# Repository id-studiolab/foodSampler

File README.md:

# foodSampler
Food sampler is a project to collect user data about their food consumption.
It consist of a series of devices equipped with buttons who can send and save data to a server using Lora protocol.

## The device
The devices are based on adafruit feather lora baord, and make use of a custom pcb.
They run on buttery and try to send messages to the lora network every 10 minutes.
once a button is pressed, they connect to the server and send out the data. A button cannot be pressed continuosly... a trasmission need to finish before a new message can be sent.
Arduino code, pcb design and more information on how to configure the library can be found inside the device folder.

## The server
The device communicate via a gateway to the things network, each device need to be configured and provisioned via ttn platform before it can send data to the server.
The server listens for incoming messages from the things network and saves the data to a mongodb DB. The data are accessible trough rest api.
More information on how to deploy the server and which api are accessible can be found in the server folder.

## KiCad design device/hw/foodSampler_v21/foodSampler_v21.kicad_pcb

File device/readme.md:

To set up the feather install the MCCI LoRaWAN LMIC library via the library manager.

Then navigate to the library folder and modify the file project_config/lmic_project_config.h with the correct frequency

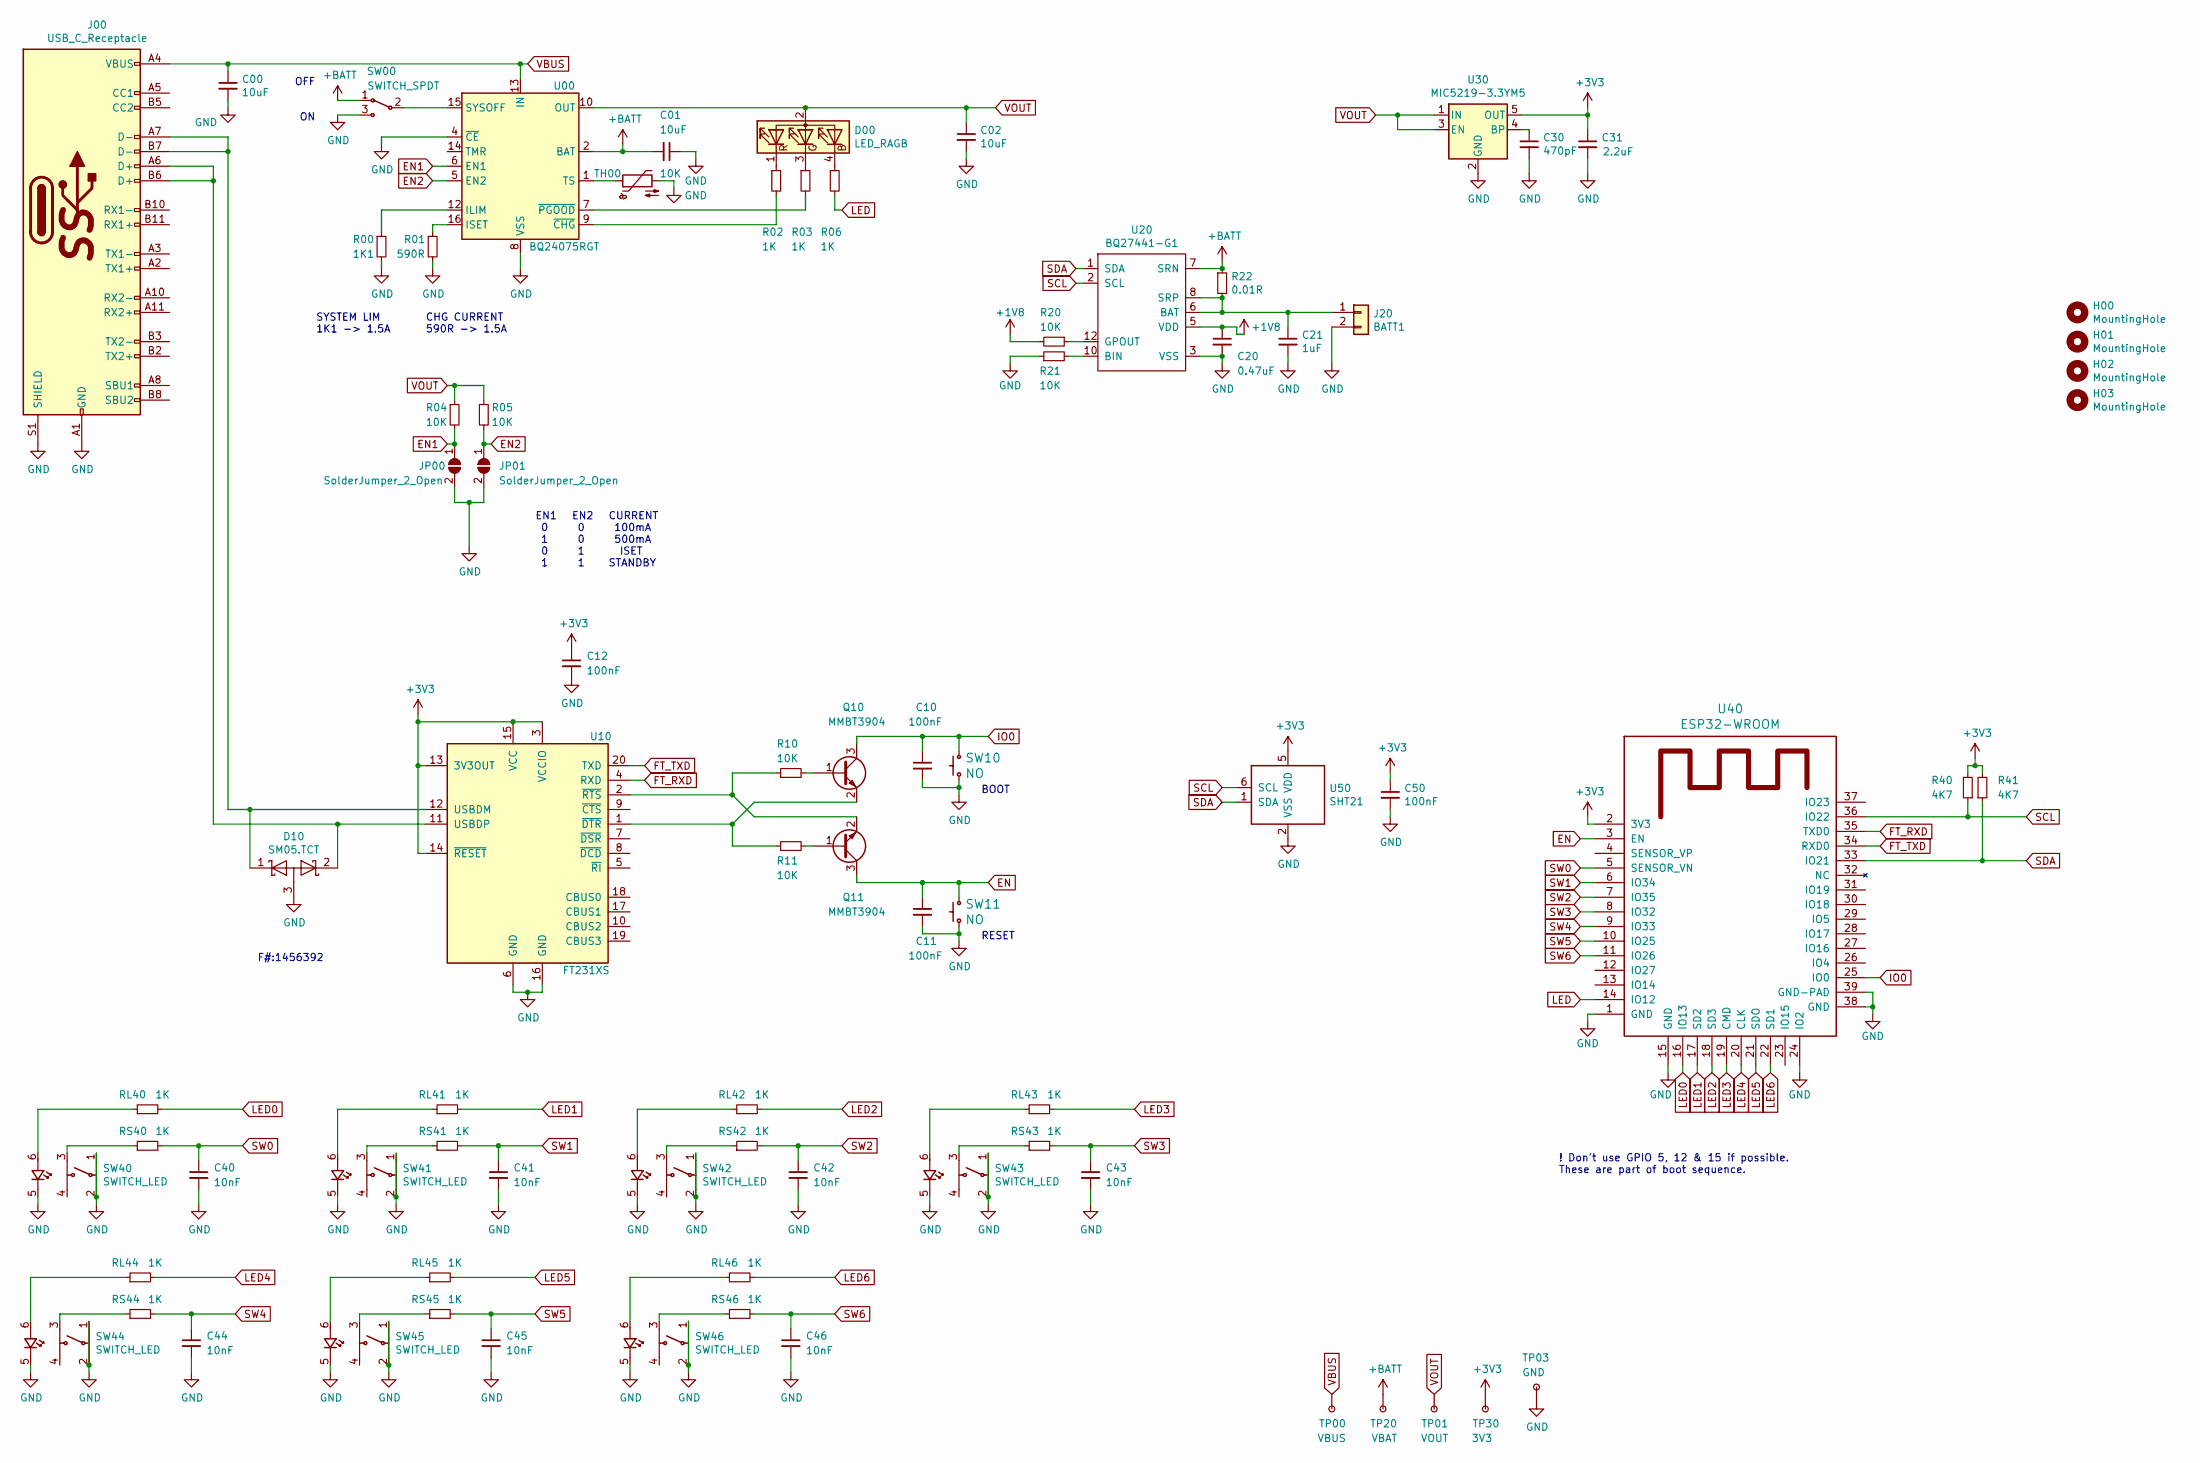
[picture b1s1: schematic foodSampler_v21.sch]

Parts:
C00, C01, C02: 10uF; C_0805_2012Metric
C10, C11, C12, C50: 100nF; C_0603_1608Metric
C20: 0.47uF; C_0603_1608Metric
C21: 1uF; C_0603_1608Metric
C30: 470pF; C_0603_1608Metric
C31: 2.2uF; CP_EIA-3216-10_Kemet-I
C40, C41, C42, C43, C44, C45, C46: 10nF; C_0603_1608Metric
D00: LED_RAGB; SMD_RGB_SIDE-APFA3010LSEEZGKQBKC
D10: SM05.TCT; SOT-23
H00, H01, H02, H03: MountingHole; MountingHole_3.2mm_M3
J00: USB_C_Receptacle; CUI_USB-C_UJ31-CH-3-MSMT-TR-67
J20: BATT1; JST_B2B-PH-K-S_SUNK
JP00, JP01: SolderJumper_2_Open; SolderJumper-2_P1.3mm_Open_RoundedPad1.0x1.5mm
Q10, Q11: MMBT3904; SOT-23
R00: 1K1; R_0603_1608Metric
R01: 590R; R_0603_1608Metric
R02, R03, R06: 1K; R_0603_1608Metric
R04, R05, R10, R11, R20, R21: 10K; R_0603_1608Metric
R22: 0.01R; C_1206_3216Metric
R40, R41: 4K7; R_0603_1608Metric
RL40, RL41, RL42, RL43, RL44, RL45, RL46: 1K; R_0603_1608Metric
RS40, RS41, RS42, RS43, RS44, RS45, RS46: 1K; R_0603_1608Metric
SW00: SWITCH_SPDT; C&K-OS102011MS2QN1_side_mount
SW10, SW11: NO; SW_SPST_4x3
SW40, SW41, SW42, SW43, SW44, SW45, SW46: SWITCH_LED; MICRO_SW_LED
TH00: 10K; R_Axial_DIN0204_L3.6mm_D1.6mm_P2.54mm_Vertical
TP00: VBUS; TEST_PAD_HOLE_1mm
TP01: VOUT; TEST_PAD_HOLE_1mm
TP03: GND; TEST_PAD_HOLE_1mm
TP20: VBAT; TEST_PAD_HOLE_1mm
TP30: 3V3; TEST_PAD_HOLE_1mm
U00: BQ24075RGT; VQFN-16-1EP_3x3mm_P0.5mm_EP1.6x1.6mm
U10: FT231XS; SSOP-20_3.9x8.7mm_P0.635mm
U20: BQ27441-G1; Texas_S-PDSO-N12
U30: MIC5219-3.3YM5; SOT-23-5
U40: ESP32-WROOM; ESP32-WROOM-32
U50: SHT21

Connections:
+1V8: C20.1, R20.2, U20.5 (VDD)
+3V3: C12.1, C31.1, C50.1, R40.2, R41.2, TP30.1, U10.3 (VCCIO), U10.13 (3V3OUT), U10.14 (~RESET), U10.15 (VCC), U30.5 (OUT), U40.2 (3V3), U50.5 (VDD)
+BATT: C01.2, R22.1, SW00.1, TP20.1, U00.2 (BAT), U00.3 (BAT), U20.7 (SRN)
EN: C11.1, Q11.3 (C), SW11.2 (B0), U40.3 (EN)
EN1: JP00.1 (A), R04.2, U00.6 (EN1)
EN2: JP01.1 (A), R05.2, U00.5 (EN2)
FT_RXD: U10.4 (RXD), U40.35 (TXD0)
FT_TXD: U10.20 (TXD), U40.34 (RXD0)
GND: C00.2, C01.1, C02.2, C10.2, C11.2, C12.2, C20.2, C21.2, C30.2, C31.2, C40.2, C41.2, C42.2, C43.2, C44.2, C45.2, C46.2, C50.2, D10.3 (A), J00.A1 (GND), J00.A12 (GND), J00.B1 (GND), J00.B12 (GND), J00.S1 (SHIELD), J20.2, JP00.2 (B), JP01.2 (B), R00.2, R01.2, R21.1, SW00.3, SW10.1 (A0), SW11.1 (A0), SW40.1, SW40.2, SW40.5, SW41.1, SW41.2, SW41.5, SW42.1, SW42.2, SW42.5, SW43.1, SW43.2, SW43.5, SW44.1, SW44.2, SW44.5, SW45.1, SW45.2, SW45.5, SW46.1, SW46.2, SW46.5, TH00.2, TP03.1, U00.4 (~CE), U00.8 (VSS), U00.17 (VSS), U10.6 (GND), U10.16 (GND), U20.3 (VSS), U30.2 (GND), U40.1 (GND), U40.15 (GND), U40.24 (IO2), U40.38 (GND), U40.39 (GND-PAD), U50.2 (VSS)
IO0: C10.1, Q10.3 (C), SW10.2 (B0), U40.25 (IO0)
LED: R06.2, U40.14 (IO12)
LED0: RL40.2, U40.16 (IO13)
LED1: RL41.2, U40.17 (SD2)
LED2: RL42.2, U40.18 (SD3)
LED3: RL43.2, U40.19 (CMD)
LED4: RL44.2, U40.20 (CLK)
LED5: RL45.2, U40.21 (SDO)
LED6: RL46.2, U40.22 (SD1)
unnamed: C21.1, J20.1, R22.2, U20.6 (BAT), U20.8 (SRP)
unnamed: C30.1, U30.4 (BP)
unnamed: D00.1 (RK), R02.1
unnamed: D00.3 (GK), R03.1
unnamed: D00.4 (BK), R06.1
unnamed: D10.1 (K), J00.A7 (D-), J00.B7 (D-), U10.12 (USBDM)
unnamed: D10.2 (K), J00.A6 (D+), J00.B6 (D+), U10.11 (USBDP)
unnamed: Q10.1 (B), R10.2
unnamed: Q10.2 (E), R11.1, U10.1 (~DTR)
unnamed: Q11.1 (B), R11.2
unnamed: Q11.2 (E), R10.1, U10.2 (~RTS)
unnamed: R00.1, U00.12 (ILIM)
unnamed: R01.1, U00.16 (ISET)
unnamed: R02.2, U00.9 (~CHG)
unnamed: R03.2, U00.7 (~PGOOD)
unnamed: R20.1, U20.12 (GPOUT)
unnamed: R21.2, U20.10 (BIN)
unnamed: RL40.1, SW40.6
unnamed: RL41.1, SW41.6
unnamed: RL42.1, SW42.6
unnamed: RL43.1, SW43.6
unnamed: RL44.1, SW44.6
unnamed: RL45.1, SW45.6
unnamed: RL46.1, SW46.6
unnamed: RS40.1, SW40.3
unnamed: RS41.1, SW41.3
unnamed: RS42.1, SW42.3
unnamed: RS43.1, SW43.3
unnamed: RS44.1, SW44.3
unnamed: RS45.1, SW45.3
unnamed: RS46.1, SW46.3
unnamed: SW00.2, U00.15 (SYSOFF)
unnamed: TH00.1, U00.1 (TS)
SCL: R40.1, U20.2 (SCL), U40.36 (IO22), U50.6 (SCL)
SDA: R41.1, U20.1 (SDA), U40.33 (IO21), U50.1 (SDA)
SW0: C40.1, RS40.2, U40.5 (SENSOR_VN)
SW1: C41.1, RS41.2, U40.6 (IO34)
SW2: C42.1, RS42.2, U40.7 (IO35)
SW3: C43.1, RS43.2, U40.8 (IO32)
SW4: C44.1, RS44.2, U40.9 (IO33)
SW5: C45.1, RS45.2, U40.10 (IO25)
SW6: C46.1, RS46.2, U40.11 (IO26)
VBUS: C00.1, J00.A4 (VBUS), J00.A9 (VBUS), J00.B4 (VBUS), J00.B9 (VBUS), TP00.1, U00.13 (IN)
VOUT: C02.1, D00.2 (A), R04.1, R05.1, TP01.1, U00.10 (OUT), U00.11 (OUT), U30.1 (IN), U30.3 (EN)

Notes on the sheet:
F#:1456392
RESET
BOOT
! Don’t use GPIO 5, 12 & 15 if possible. These are part of boot sequence.
CHG CURRENT 590R -> 1.5A
SYSTEM LIM 1K1 -> 1.5A
EN1 0 1 0 1
EN2 0 0 1 1
CURRENT 100mA 500mA ISET STANDBY
OFF ON

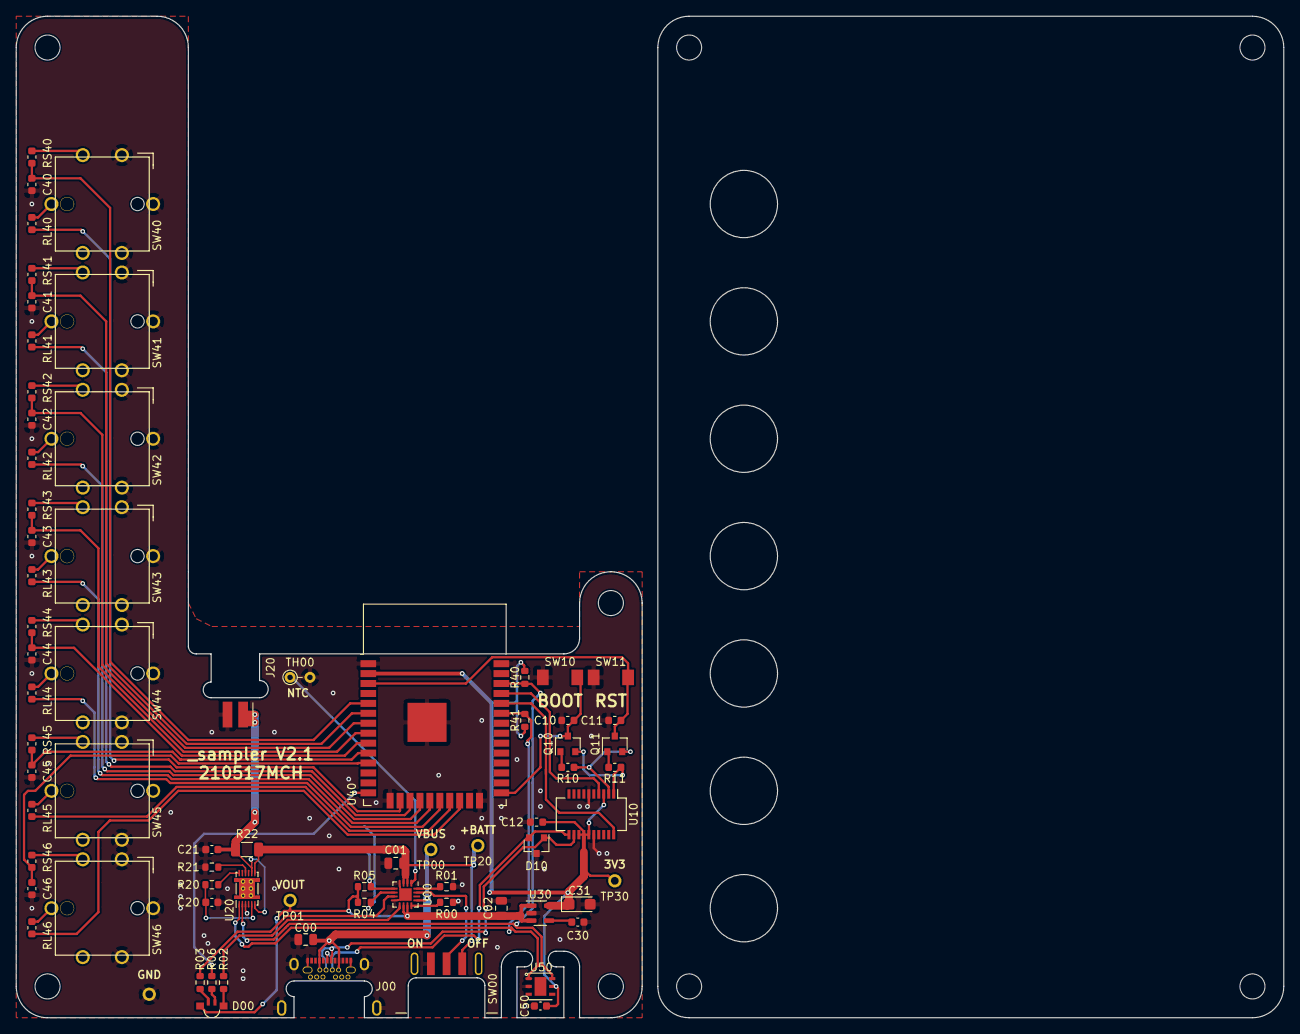
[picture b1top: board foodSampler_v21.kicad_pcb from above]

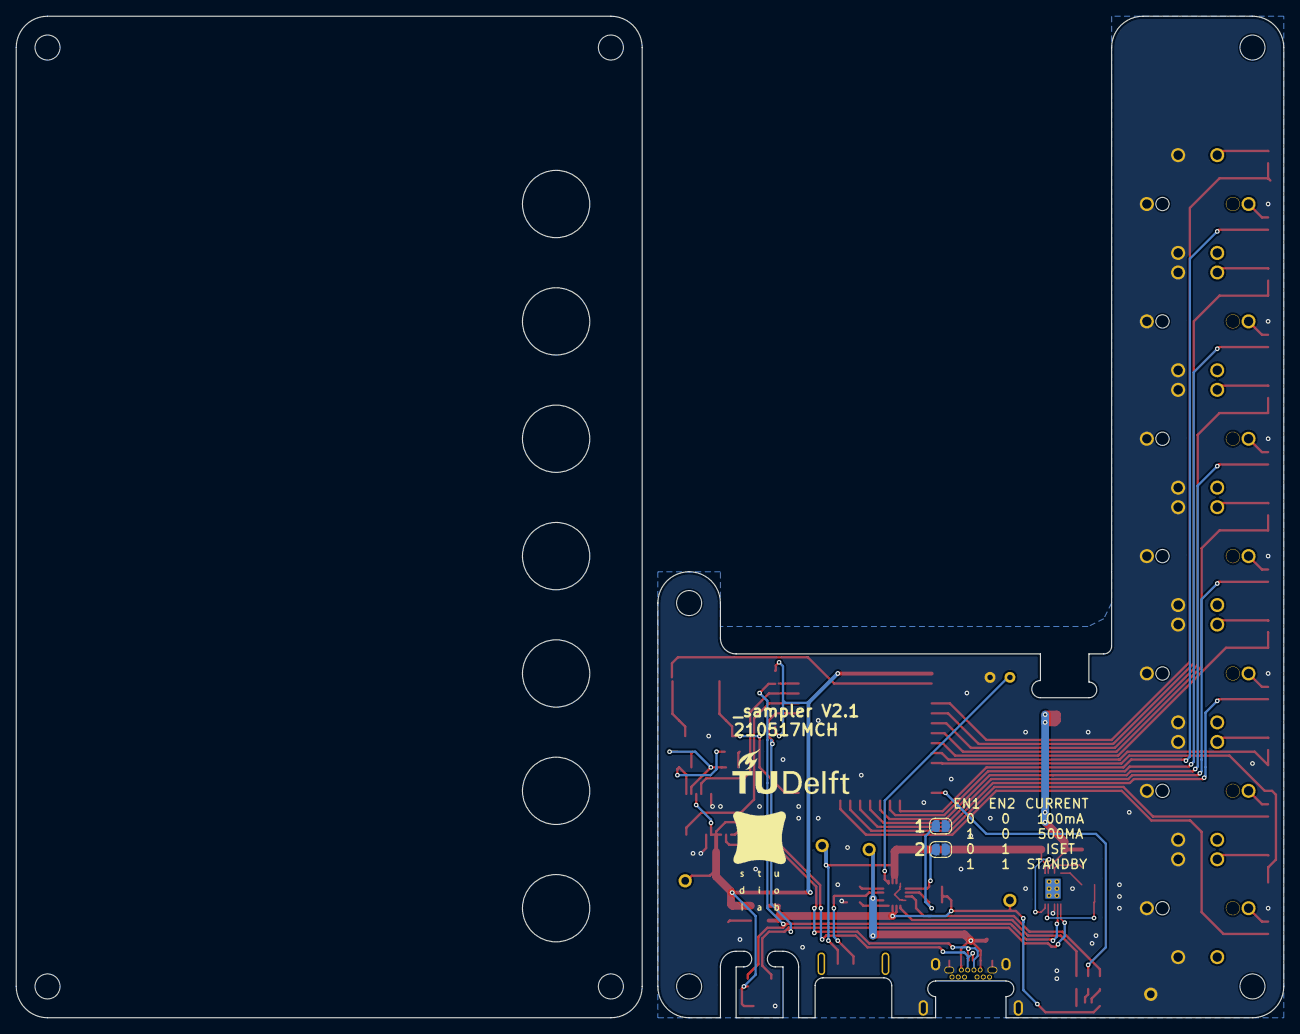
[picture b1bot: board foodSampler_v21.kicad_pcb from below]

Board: 2 copper layers, 162.0 x 128.0 mm, 84 parts (2 on the bottom side), 62 nets.

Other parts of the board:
H01#2, H01#3, H01#4, H01#5: MountingHole; MountingHole_3.2mm_M3

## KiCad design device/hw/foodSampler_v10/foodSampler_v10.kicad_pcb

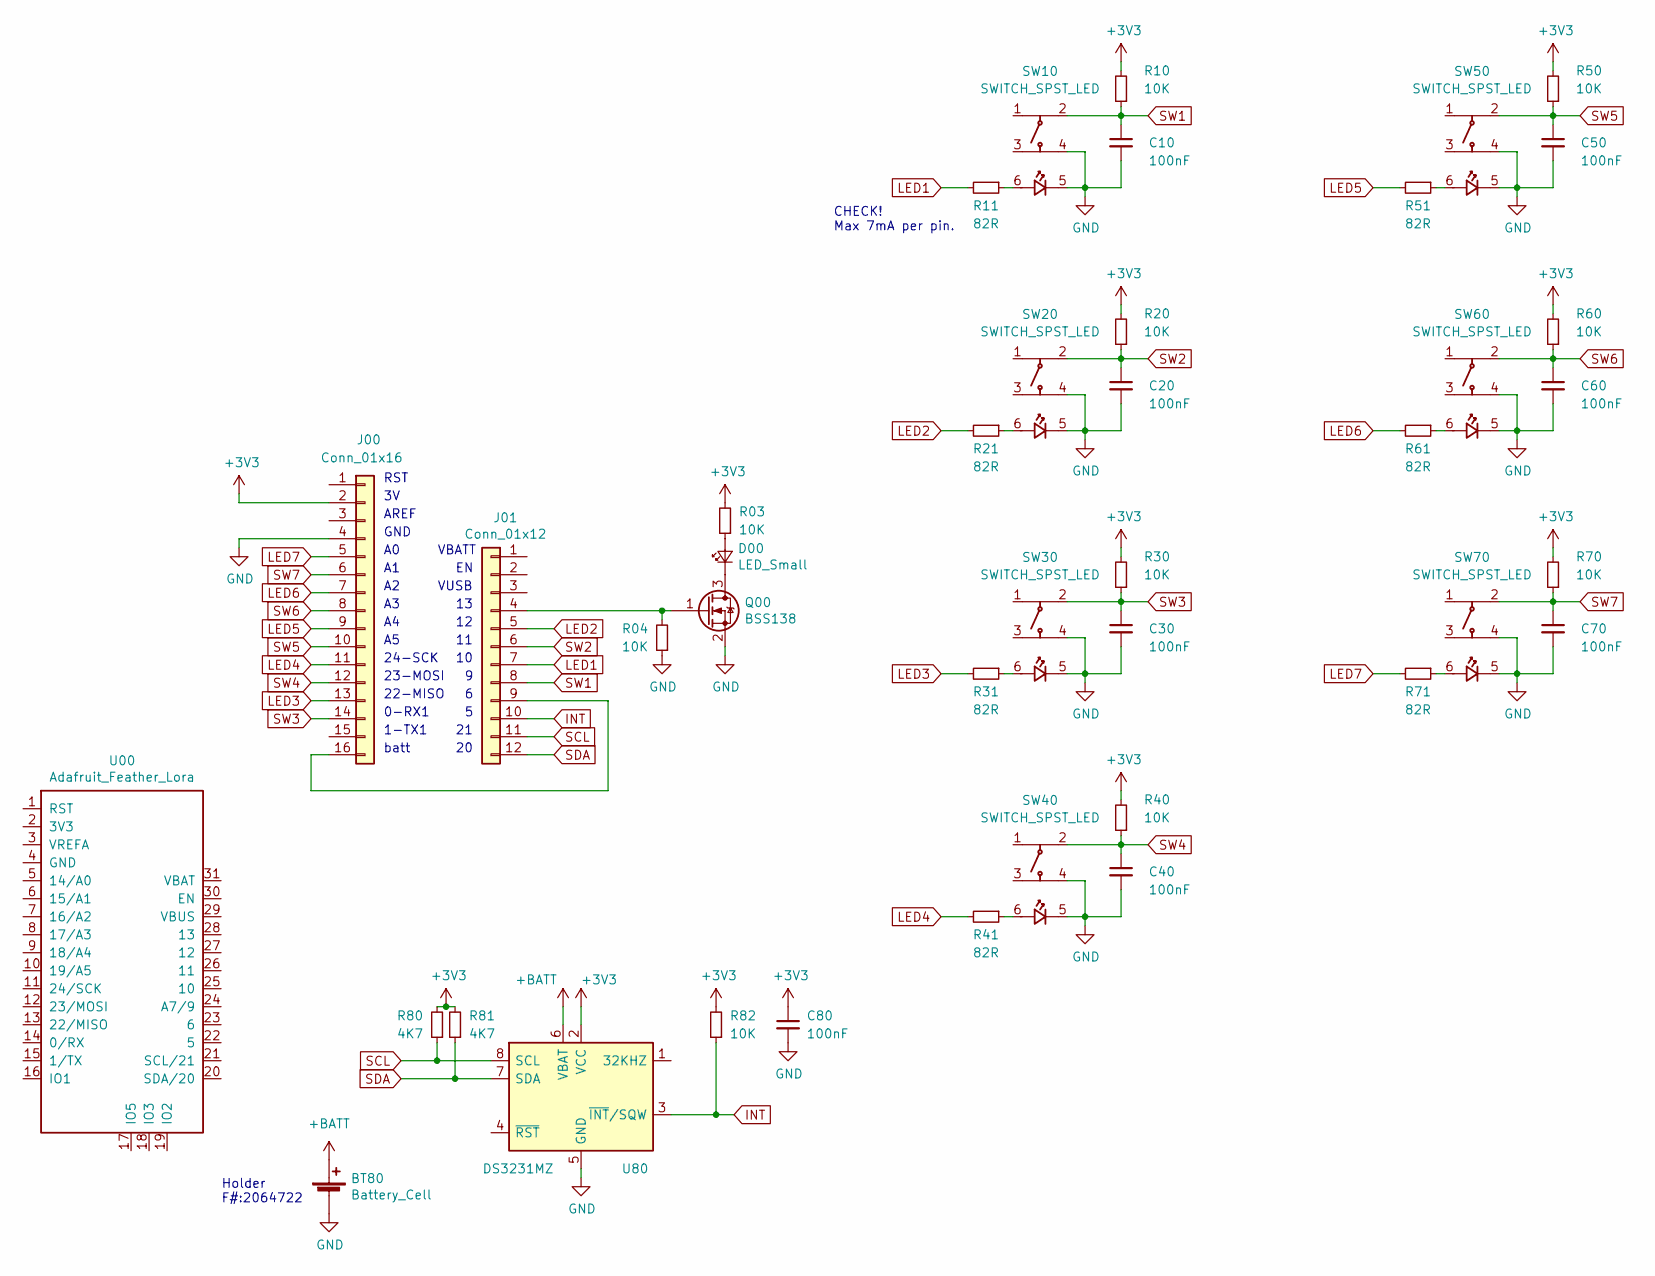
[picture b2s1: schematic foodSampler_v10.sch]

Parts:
BT80: Battery_Cell; CH291-1220LF
C10, C20, C30, C40, C50, C60, C70, C80: 100nF; C_0603_1608Metric
D00: LED_Small; LED_1206_3216Metric
J00: Conn_01x16; PinHeader_1x16_P2.54mm_Vertical_SMD_Pin1Left
J01: Conn_01x12; PinHeader_1x12_P2.54mm_Vertical_SMD_Pin1Left
Q00: BSS138; SOT-23
R03, R04, R10, R20, R30, R40, R50, R60, R70, R82: 10K; R_0603_1608Metric
R11, R21, R31, R41, R51, R61, R71: 82R; R_0603_1608Metric
R80, R81: 4K7; R_0603_1608Metric
SW10, SW20, SW30, SW40, SW50, SW60, SW70: SWITCH_SPST_LED; MICRO_SW_LED
U00: Adafruit_Feather_Lora; Adafruit Feather LORA
U80: DS3231MZ; SOIC-8_3.9x4.9mm_P1.27mm

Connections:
+3V3: C80.1, J00.2, R03.2, R10.2, R20.2, R30.2, R40.2, R50.2, R60.2, R70.2, R80.2, R81.2, R82.2, U80.2 (VCC)
+BATT: BT80.1 (+), U80.6 (VBAT)
GND: BT80.2 (-), C10.2, C20.2, C30.2, C40.2, C50.2, C60.2, C70.2, C80.2, J00.4, Q00.2 (S), R04.1, SW10.4, SW10.5, SW20.4, SW20.5, SW30.4, SW30.5, SW40.4, SW40.5, SW50.4, SW50.5, SW60.4, SW60.5, SW70.4, SW70.5, U80.5 (GND)
INT: J01.10, R82.1, U80.3 (~INT~/SQW)
LED1: J01.7, R11.2
LED2: J01.5, R21.2
LED3: J00.13, R31.2
LED4: J00.11, R41.2
LED5: J00.9, R51.2
LED6: J00.7, R61.2
LED7: J00.5, R71.2
unnamed: D00.1 (K), Q00.3 (D)
unnamed: D00.2 (A), R03.1
unnamed: J00.16, J01.9
unnamed: J01.4, Q00.1 (G), R04.2
unnamed: R11.1, SW10.6
unnamed: R21.1, SW20.6
unnamed: R31.1, SW30.6
unnamed: R41.1, SW40.6
unnamed: R51.1, SW50.6
unnamed: R61.1, SW60.6
unnamed: R71.1, SW70.6
SCL: J01.11, R80.1, U80.8 (SCL)
SDA: J01.12, R81.1, U80.7 (SDA)
SW1: C10.1, J01.8, R10.1, SW10.2
SW2: C20.1, J01.6, R20.1, SW20.2
SW3: C30.1, J00.14, R30.1, SW30.2
SW4: C40.1, J00.12, R40.1, SW40.2
SW5: C50.1, J00.10, R50.1, SW50.2
SW6: C60.1, J00.8, R60.1, SW60.2
SW7: C70.1, J00.6, R70.1, SW70.2

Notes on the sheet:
CHECK! Max 7mA per pin.
Holder F#:2064722
batt
1-TX1
0-RX1
22-MISO
23-MOSI
24-SCK
GND
AREF
RST
VUSB
VBATT

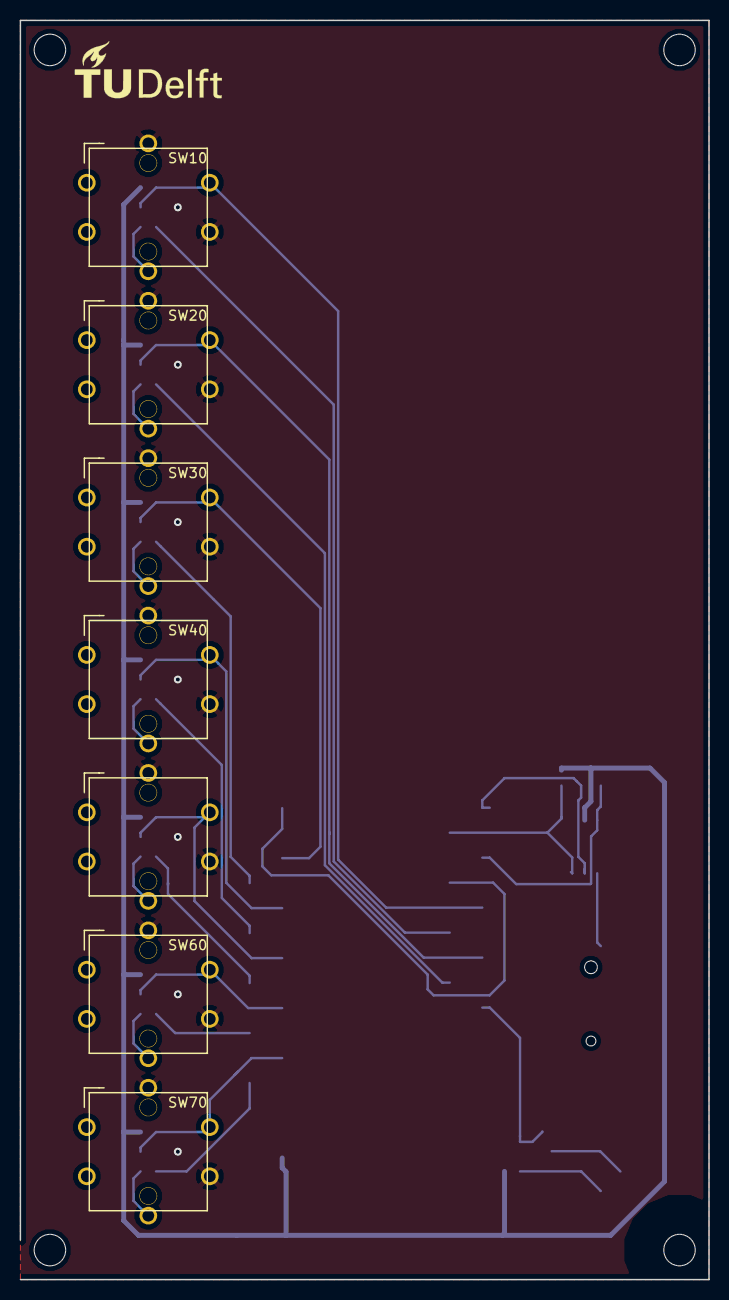
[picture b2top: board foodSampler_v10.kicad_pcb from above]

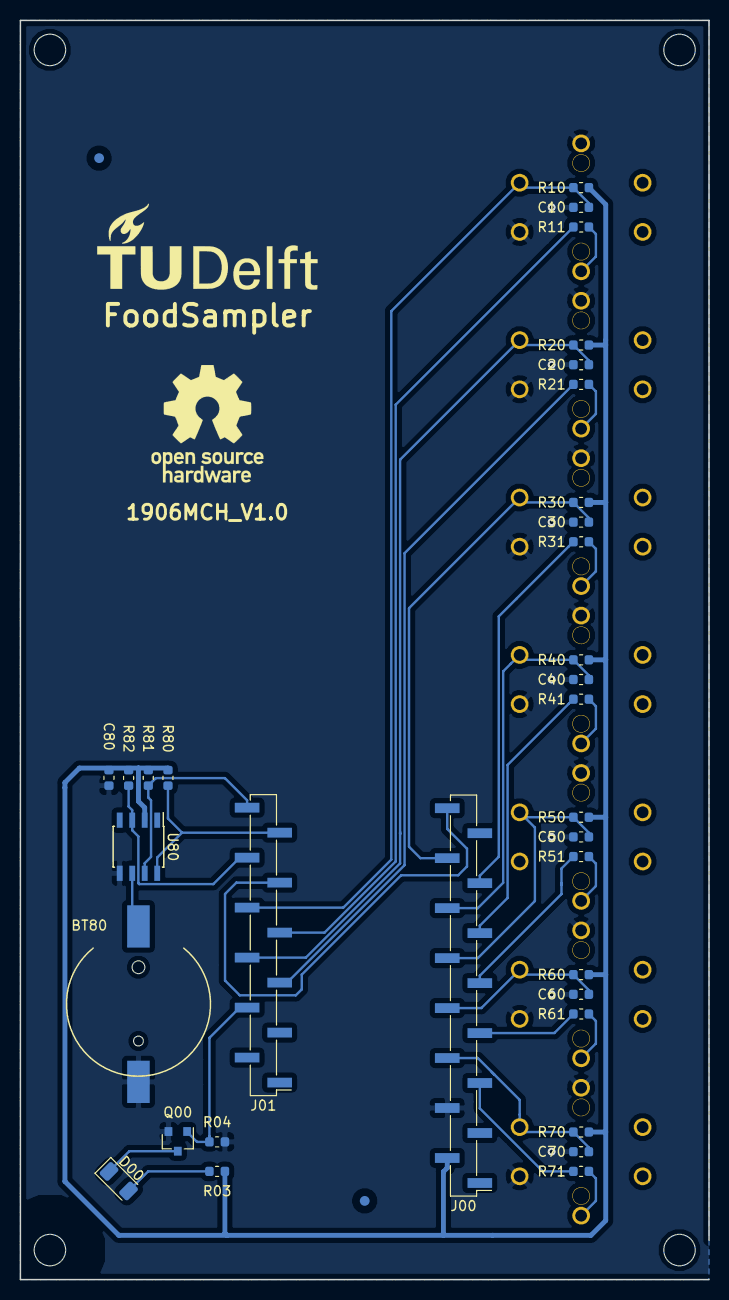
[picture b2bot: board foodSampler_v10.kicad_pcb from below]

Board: 2 copper layers, 70.0 x 128.0 mm, 40 parts (33 on the bottom side), 31 nets.

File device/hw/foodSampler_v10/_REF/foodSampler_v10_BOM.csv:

"Id";"Designator";"Package";"Quantity";"Designation";"Supplier and ref";
1;"J00";"PinHeader_1x16_P2.54mm_Vertical_SMD_Pin1Left";1;"Conn_01x16";;;
2;"C10,C20,C30,C40,C50,C60,C70,C80";"C_0603_1608Metric";8;"100nF";;;
3;"R10,R20,R30,R40,R50,R60,R70,R03,R82,R04";"R_0603_1608Metric";10;"10K";;;
4;"R11,R21,R31,R41,R51,R61,R71";"R_0603_1608Metric";7;"82R";;;
5;"SW10,SW20,SW30,SW40,SW50,SW60,SW70";"MICRO_SW_LED";7;"SWITCH_SPST_LED";;;
6;"REF**";"LIPO_3V7_2A_50x60";1;"LIPO_3V7_2A_50x60";;;
7;"J01";"PinHeader_1x12_P2.54mm_Vertical_SMD_Pin1Left";1;"Conn_01x12";;;
8;"R80,R81";"R_0603_1608Metric";2;"4K7";;;
9;"U80";"SOIC-8_3.9x4.9mm_P1.27mm";1;"DS3231MZ";;;
10;"D00";"LED_1206_3216Metric";1;"LED_Small";;;
11;"BT80";"CH291-1220LF";1;"Battery_Cell";;;
12;"Q00";"SOT-23";1;"BSS138";;;
13;"REF**,REF**,REF**,REF**";"MountingHole_3.2mm_M3_DIN965";4;"MountingHole_3.2mm_M3_DIN965";;;
14;"REF**,REF**";"Fiducial_1mm_Dia_2.54mm_Outer_CopperBottom";2;"Fiducial_1mm_Dia_2.54mm_Outer_CopperBottom";;;
15;"G***";"TUDelft_15x5.9";1;"LOGO";;;
16;"REF**";"OSHW-Logo_11.4x12mm_SilkScreen";1;"OSHW-Logo_11.4x12mm_SilkScreen";;;
17;"G***";"TUDelft_22.5x8.8";1;"LOGO";;;

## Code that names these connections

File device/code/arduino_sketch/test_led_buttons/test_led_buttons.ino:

#define BUT0   9
#define BUT1   11
#define BUT2   0
#define BUT3   1
#define BUT4   A5
#define BUT5   A3
#define BUT6   A1
#define BATPIN A7
#define LED    13

#define LED0   10
#define LED1   12
#define LED2   22
#define LED3   24
#define LED4   A4
#define LED5   A2
#define LED6   A0

int buttons[] = {BUT0, BUT1, BUT2, BUT3, BUT4, BUT5, BUT6, BUT6};
int leds[] = {LED0, LED1, LED2, LED3, LED4, LED5, LED6, LED6};

void setup() {

  for (int i = 0; i < 7; i++) {
    pinMode(buttons[i], INPUT_PULLUP);
    pinMode(leds[i], OUTPUT);
  }
  Serial.begin(9600);
}

void loop() {
  for (int i = 0; i < 7; i++) {
    if (digitalRead(buttons[i])==LOW){
      digitalWrite(leds[i],HIGH);
      Serial.print("button "); 
      Serial.print(i);
      Serial.println(" was pressed");
    }else{
      digitalWrite(leds[i],LOW);
    }
  }
}

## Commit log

2019-03-29 added readme
2019-04-11 add server boilerplate
2019-04-17 intial rest api development
2019-04-18 events model
2019-04-18 created basic api
2019-04-26 got harware working
2019-04-26 add instruction on how to modify the library
2019-04-26 done parsing data from device - need to modify device property in rest api
2019-05-08 updated server api
2019-05-15 added mosca broker and code to forward messages to mqtt
2019-05-15 ready for first test
2019-05-15 modified mosquitto publishing address
2019-05-15 fixes variable missing
2019-05-15 fix wrong addressess for different environment
2019-05-15 Added working protoype code
2019-05-30 fixes apidoc
2019-05-30 ported project to gulp 4
2019-05-30 removed wrong dependency
2019-06-19 add authentication
2019-06-19 schematic added
2019-06-21 tryign to fix things
2019-06-21 V1.0, all working
2019-06-21 fixes authentication
2019-06-21 modified app name
2019-06-21 missind gependency
2019-06-21 typo
2019-06-21 all working
2019-06-21 add files to keep credentials
2019-06-21 led solved
2019-06-21 led solved + flash sequences
2019-06-21 fixes server crashing when data is coming from unknown device
2019-06-21 debug mode and rtc added
2019-07-01 regenerated doc
2019-07-01 re-enabled account creation
2019-07-02 impreoved doc and fixed minor bug
2019-07-02 add filter mechanism for api
2019-08-20 adding cors support to server
2019-08-20 fixes filter events by date range
2019-08-21 fixes dates interval not working
2019-10-03 created new case
2019-10-28 updated 3d printed files
2019-10-28 provisioned all the devices id
2019-10-28 add nickname to device
2019-10-28 remove authentification to create events
2019-10-29 Bump mongoose from 5.5.11 to 5.7.5 in /server/foodsampler
    Bumps [mongoose](https://github.com/Automattic/mongoose) from 5.5.11 to 5.7.5.
    - [Release notes](https://github.com/Automattic/mongoose/releases)
    - [Changelog](https://github.com/Automattic/mongoose/blob/master/History.md)
    - [Commits](https://github.com/Automattic/mongoose/compare/5.5.11...5.7.5)
2019-10-30 to compare
2019-10-30 new send routines
2019-10-30 version 2
2019-10-31 minor changes
2019-10-31 refactored and cleaned cue logic
2019-11-01 fixes to the main logic
2019-11-01 seem to be working
2019-11-11 fixes data loss by forcing hack form ttn
2020-06-30 Bump express-jwt from 5.3.1 to 6.0.0 in /server/foodsampler
    Bumps [express-jwt](https://github.com/auth0/express-jwt) from 5.3.1 to 6.0.0.
    - [Release notes](https://github.com/auth0/express-jwt/releases)
    - [Changelog](https://github.com/auth0/express-jwt/blob/master/CHANGELOG.md)
    - [Commits](https://github.com/auth0/express-jwt/compare/v5.3.1...v6.0.0)
2020-07-17 Bump lodash from 4.17.11 to 4.17.19 in /server/foodsampler
    Bumps [lodash](https://github.com/lodash/lodash) from 4.17.11 to 4.17.19.
    - [Release notes](https://github.com/lodash/lodash/releases)
    - [Commits](https://github.com/lodash/lodash/compare/4.17.11...4.17.19)
2021-03-30 Bump y18n from 3.2.1 to 3.2.2 in /server/foodsampler
    Bumps [y18n](https://github.com/yargs/y18n) from 3.2.1 to 3.2.2.
    - [Release notes](https://github.com/yargs/y18n/releases)
    - [Changelog](https://github.com/yargs/y18n/blob/master/CHANGELOG.md)
    - [Commits](https://github.com/yargs/y18n/commits)
2021-04-13 added hw v2.0
2021-04-13 Bump dot-prop from 4.2.0 to 4.2.1 in /server/foodsampler
    Bumps [dot-prop](https://github.com/sindresorhus/dot-prop) from 4.2.0 to 4.2.1.
    - [Release notes](https://github.com/sindresorhus/dot-prop/releases)
    - [Commits](https://github.com/sindresorhus/dot-prop/compare/v4.2.0...v4.2.1)
2021-04-13 Bump bl from 1.2.2 to 1.2.3 in /server/foodsampler
    Bumps [bl](https://github.com/rvagg/bl) from 1.2.2 to 1.2.3.
    - [Release notes](https://github.com/rvagg/bl/releases)
    - [Commits](https://github.com/rvagg/bl/compare/v1.2.2...v1.2.3)
2021-04-13 Bump mixin-deep from 1.3.1 to 1.3.2 in /server/foodsampler
    Bumps [mixin-deep](https://github.com/jonschlinkert/mixin-deep) from 1.3.1 to 1.3.2.
    - [Release notes](https://github.com/jonschlinkert/mixin-deep/releases)
    - [Commits](https://github.com/jonschlinkert/mixin-deep/compare/1.3.1...1.3.2)
2021-04-13 Bump yargs-parser from 5.0.0 to 5.0.1 in /server/foodsampler
    Bumps [yargs-parser](https://github.com/yargs/yargs-parser) from 5.0.0 to 5.0.1.
    - [Release notes](https://github.com/yargs/yargs-parser/releases)
    - [Changelog](https://github.com/yargs/yargs-parser/blob/v5.0.1/CHANGELOG.md)
    - [Commits](https://github.com/yargs/yargs-parser/compare/v5.0.0...v5.0.1)
2021-04-13 datasheets added
2021-05-08 Bump lodash from 4.17.11 to 4.17.21 in /server/foodsampler
    Bumps [lodash](https://github.com/lodash/lodash) from 4.17.11 to 4.17.21.
    - [Release notes](https://github.com/lodash/lodash/releases)
    - [Commits](https://github.com/lodash/lodash/compare/4.17.11...4.17.21)
2021-05-08 Bump bson from 1.1.1 to 1.1.6 in /server/foodsampler
    Bumps [bson](https://github.com/mongodb/js-bson) from 1.1.1 to 1.1.6.
    - [Release notes](https://github.com/mongodb/js-bson/releases)
    - [Changelog](https://github.com/mongodb/js-bson/blob/v1.1.6/HISTORY.md)
    - [Commits](https://github.com/mongodb/js-bson/commits/v1.1.6)
2021-05-10 Bump hosted-git-info from 2.7.1 to 2.8.9 in /server/foodsampler
    Bumps [hosted-git-info](https://github.com/npm/hosted-git-info) from 2.7.1 to 2.8.9.
    - [Release notes](https://github.com/npm/hosted-git-info/releases)
    - [Changelog](https://github.com/npm/hosted-git-info/blob/v2.8.9/CHANGELOG.md)
    - [Commits](https://github.com/npm/hosted-git-info/compare/v2.7.1...v2.8.9)
2021-05-12 Bump grpc from 1.21.1 to 1.24.9 in /server/foodsampler
    Bumps [grpc](https://github.com/grpc/grpc-node) from 1.21.1 to 1.24.9.
    - [Release notes](https://github.com/grpc/grpc-node/releases)
    - [Commits](https://github.com/grpc/grpc-node/commits)
2021-05-21 V2.1 added
2021-05-25 Bump browserslist from 4.6.1 to 4.16.6 in /server/foodsampler
    Bumps [browserslist](https://github.com/browserslist/browserslist) from 4.6.1 to 4.16.6.
    - [Release notes](https://github.com/browserslist/browserslist/releases)
    - [Changelog](https://github.com/browserslist/browserslist/blob/main/CHANGELOG.md)
    - [Commits](https://github.com/browserslist/browserslist/compare/4.6.1...4.16.6)
2021-06-10 _sampler V2.2 added
2021-06-15 small revisions
2021-08-11 Bump path-parse from 1.0.6 to 1.0.7 in /server/foodsampler
    Bumps [path-parse](https://github.com/jbgutierrez/path-parse) from 1.0.6 to 1.0.7.
    - [Release notes](https://github.com/jbgutierrez/path-parse/releases)
    - [Commits](https://github.com/jbgutierrez/path-parse/commits/v1.0.7)
    ---
    updated-dependencies:
    - dependency-name: path-parse
2022-02-10 Bump undefsafe from 2.0.2 to 2.0.5 in /server/foodsampler
    Bumps [undefsafe](https://github.com/remy/undefsafe) from 2.0.2 to 2.0.5.
    - [Release notes](https://github.com/remy/undefsafe/releases)
    - [Commits](https://github.com/remy/undefsafe/compare/v2.0.2...v2.0.5)
    ---
    updated-dependencies:
    - dependency-name: undefsafe
2022-02-11 Bump ajv from 6.10.0 to 6.12.6 in /server/foodsampler
    Bumps [ajv](https://github.com/ajv-validator/ajv) from 6.10.0 to 6.12.6.
    - [Release notes](https://github.com/ajv-validator/ajv/releases)
    - [Commits](https://github.com/ajv-validator/ajv/compare/v6.10.0...v6.12.6)
    ---
    updated-dependencies:
    - dependency-name: ajv
2022-06-27 Bump copy-props from 2.0.4 to 2.0.5 in /server/foodsampler
    Bumps [copy-props](https://github.com/gulpjs/copy-props) from 2.0.4 to 2.0.5.
    - [Release notes](https://github.com/gulpjs/copy-props/releases)
    - [Changelog](https://github.com/gulpjs/copy-props/blob/master/CHANGELOG.md)
    - [Commits](https://github.com/gulpjs/copy-props/compare/2.0.4...2.0.5)
    ---
    updated-dependencies:
2022-12-03 Bump decode-uri-component from 0.2.0 to 0.2.2 in /server/foodsampler
    Bumps [decode-uri-component](https://github.com/SamVerschueren/decode-uri-component) from 0.2.0 to 0.2.2.
    - [Release notes](https://github.com/SamVerschueren/decode-uri-component/releases)
    - [Commits](https://github.com/SamVerschueren/decode-uri-component/compare/v0.2.0...v0.2.2)
    ---
    updated-dependencies:
    - dependency-name: decode-uri-component
2022-12-09 Bump qs and express in /server/foodsampler
    Bumps [qs](https://github.com/ljharb/qs) to 6.5.3 and updates ancestor dependency [express](https://github.com/expressjs/express). These dependencies need to be updated together.
    Updates `qs` from 6.5.2 to 6.5.3
    - [Release notes](https://github.com/ljharb/qs/releases)
    - [Changelog](https://github.com/ljharb/qs/blob/main/CHANGELOG.md)
    - [Commits](https://github.com/ljharb/qs/compare/v6.5.2...v6.5.3)
    Updates `express` from 4.16.4 to 4.18.2
2022-12-09 Bump express from 4.16.4 to 4.17.3 in /server/foodsampler
    Bumps [express](https://github.com/expressjs/express) from 4.16.4 to 4.17.3.
    - [Release notes](https://github.com/expressjs/express/releases)
    - [Changelog](https://github.com/expressjs/express/blob/master/History.md)
    - [Commits](https://github.com/expressjs/express/compare/4.16.4...4.17.3)
    ---
    updated-dependencies:
2023-01-03 Bump json5 from 2.1.0 to 2.2.3 in /server/foodsampler
    Bumps [json5](https://github.com/json5/json5) from 2.1.0 to 2.2.3.
    - [Release notes](https://github.com/json5/json5/releases)
    - [Changelog](https://github.com/json5/json5/blob/main/CHANGELOG.md)
    - [Commits](https://github.com/json5/json5/compare/v2.1.0...v2.2.3)
    ---
    updated-dependencies:
